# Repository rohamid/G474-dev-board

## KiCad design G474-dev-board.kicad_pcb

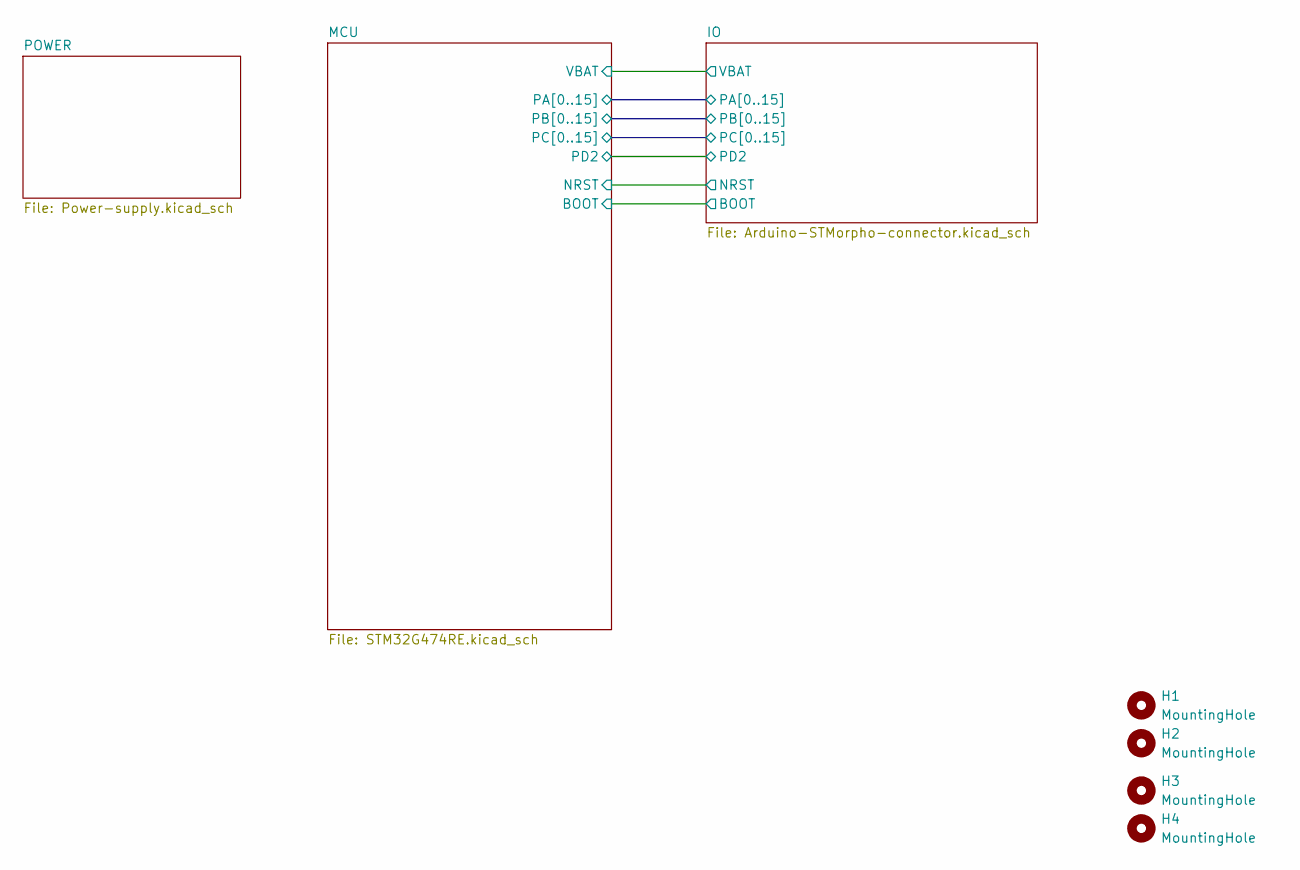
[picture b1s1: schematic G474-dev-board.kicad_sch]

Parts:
H1, H2, H3, H4: MountingHole; MountingHole_3.2mm_M3

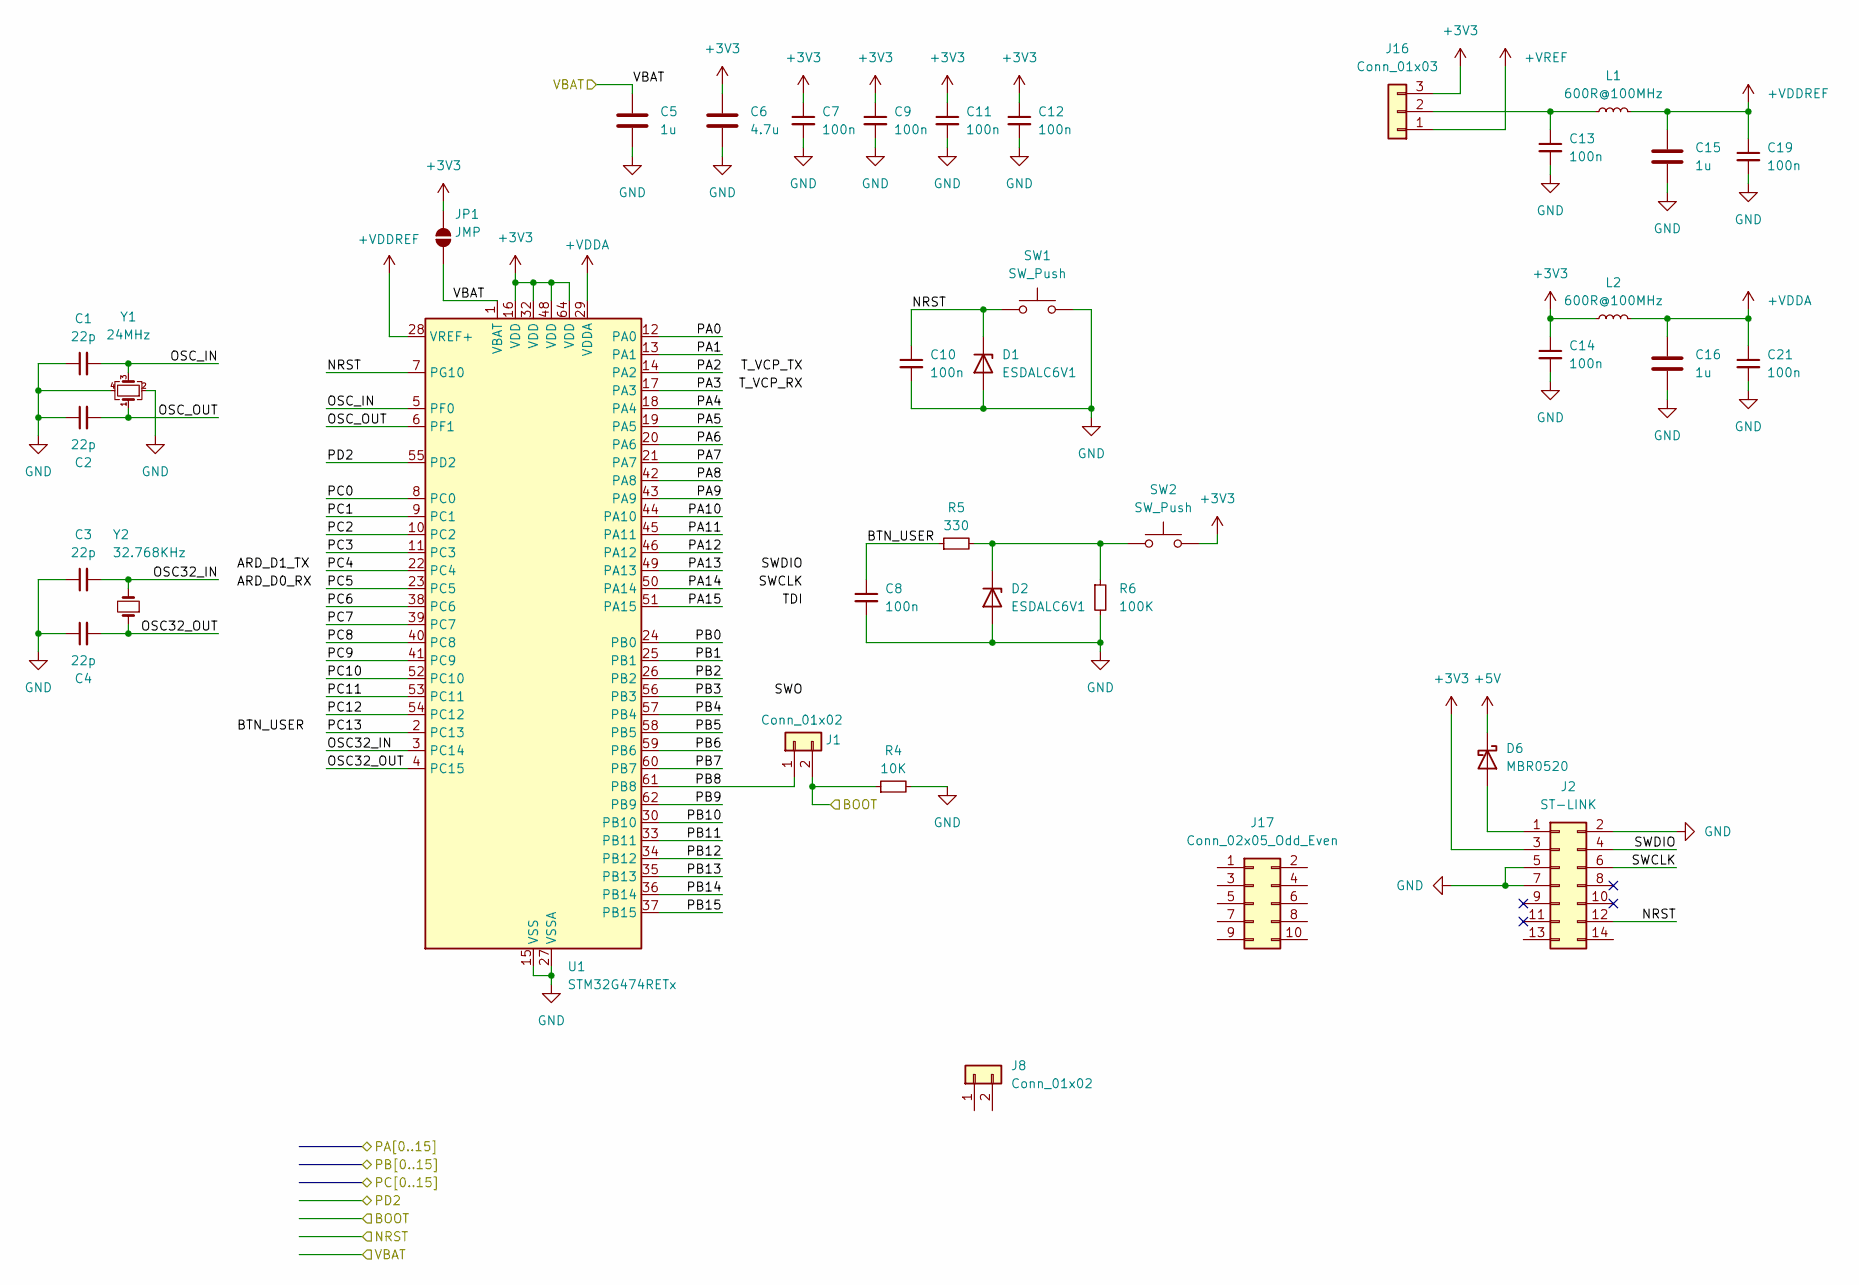
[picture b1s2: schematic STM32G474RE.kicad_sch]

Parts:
C1, C2, C3, C4: 22p; C_0603_1608Metric; JLCPCB Part # C1653
C5, C15, C16: 1u; C_0805_2012Metric; JLCPCB Part # C28323
C6: 4.7u; C_0805_2012Metric; JLCPCB Part # C1779
C7, C8, C9, C10, C11, C12, C13, C14, C19, C21: 100n; C_0603_1608Metric; JLCPCB Part # C14663
D1, D2: ESDALC6V1; D_SOD-123F; JLCPCB Part # C2990473
D6: MBR0520; D_SOD-123; JLCPCB Part # C64885
J1, J8: Conn_01x02; PinHeader_1x02_P2.54mm_Vertical
J2: ST-LINK; PinHeader_2x07_P1.27mm_Vertical_SMD
J16: Conn_01x03; PinHeader_1x03_P2.54mm_Vertical
J17: Conn_02x05_Odd_Even; IDC-Header_2x05_P2.54mm_Vertical
JP1: JMP; SolderJumper-2_P1.3mm_Open_RoundedPad1.0x1.5mm
L1, L2: 600R@100MHz; L_0805_2012Metric_Pad1.05x1.20mm_HandSolder; JLCPCB Part # C1017
R4: 10K; R_0603_1608Metric; JLCPCB Part # C25804
R5: 330; R_0603_1608Metric; JLCPCB Part # C23138
R6: 100K; R_0603_1608Metric; JLCPCB Part # C25803
SW1, SW2: SW_Push; SW_PUSH_6mm_H5mm
U1: STM32G474RETx; LQFP-64_10x10mm_P0.5mm; JLCPCB Part # C521608
Y1: 24MHz; Crystal_SMD_3225-4Pin_3.2x2.5mm; JLCPCB Part # C255917
Y2: 32.768KHz; Crystal_SMD_3215-2Pin_3.2x1.5mm; JLCPCB Part # C97606

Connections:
+3V3: C6.1, C7.1, C9.1, C11.1, C12.1, C14.1, J2.3, J16.3, JP1.2 (B), L2.1, SW2.2, U1.16 (VDD), U1.32 (VDD), U1.48 (VDD), U1.64 (VDD); also elsewhere on the board
+5V: D6.1 (K); also elsewhere on the board
+VDDA: C16.1, C21.1, L2.2, U1.29 (VDDA)
+VDDREF: C15.1, C19.1, L1.2, U1.28 (VREF+); also elsewhere on the board
+VREF: J16.1; also elsewhere on the board
/IO/BOOT: J1.2, R4.1; also elsewhere on the board
/IO/NRST: C10.1, D1.1 (K), J2.12, SW1.1, U1.7 (PG10); also elsewhere on the board
/IO/PA0: U1.12 (PA0); also elsewhere on the board
/IO/PA1: U1.13 (PA1); also elsewhere on the board
/IO/PA2: U1.14 (PA2)
/IO/PA3: U1.17 (PA3)
/IO/PA4: U1.18 (PA4); also elsewhere on the board
/IO/PA5: U1.19 (PA5); also elsewhere on the board
/IO/PA6: U1.20 (PA6); also elsewhere on the board
/IO/PA7: U1.21 (PA7); also elsewhere on the board
/IO/PA8: U1.42 (PA8); also elsewhere on the board
/IO/PA9: U1.43 (PA9); also elsewhere on the board
/IO/PA10: U1.44 (PA10); also elsewhere on the board
/IO/PA11: U1.45 (PA11); also elsewhere on the board
/IO/PA12: U1.46 (PA12); also elsewhere on the board
/IO/PA13: U1.49 (PA13); also elsewhere on the board
/IO/PA14: U1.50 (PA14); also elsewhere on the board
/IO/PA15: U1.51 (PA15); also elsewhere on the board
/IO/PB0: U1.24 (PB0); also elsewhere on the board
/IO/PB1: U1.25 (PB1); also elsewhere on the board
/IO/PB2: U1.26 (PB2); also elsewhere on the board
/IO/PB3: U1.56 (PB3); also elsewhere on the board
/IO/PB4: U1.57 (PB4); also elsewhere on the board
/IO/PB5: U1.58 (PB5); also elsewhere on the board
/IO/PB6: U1.59 (PB6); also elsewhere on the board
/IO/PB7: U1.60 (PB7); also elsewhere on the board
/IO/PB8: J1.1, U1.61 (PB8); also elsewhere on the board
/IO/PB9: U1.62 (PB9); also elsewhere on the board
/IO/PB10: U1.30 (PB10); also elsewhere on the board
/IO/PB11: U1.33 (PB11); also elsewhere on the board
/IO/PB12: U1.34 (PB12); also elsewhere on the board
/IO/PB13: U1.35 (PB13); also elsewhere on the board
/IO/PB14: U1.36 (PB14); also elsewhere on the board
/IO/PB15: U1.37 (PB15); also elsewhere on the board
/IO/PC0: U1.8 (PC0); also elsewhere on the board
/IO/PC1: U1.9 (PC1); also elsewhere on the board
/IO/PC2: U1.10 (PC2); also elsewhere on the board
/IO/PC3: U1.11 (PC3); also elsewhere on the board
/IO/PC4: U1.22 (PC4); also elsewhere on the board
/IO/PC5: U1.23 (PC5); also elsewhere on the board
/IO/PC6: U1.38 (PC6); also elsewhere on the board
/IO/PC7: U1.39 (PC7); also elsewhere on the board
/IO/PC8: U1.40 (PC8); also elsewhere on the board
/IO/PC9: U1.41 (PC9); also elsewhere on the board
/IO/PC10: U1.52 (PC10); also elsewhere on the board
/IO/PC11: U1.53 (PC11); also elsewhere on the board
/IO/PC12: U1.54 (PC12); also elsewhere on the board
/IO/PC13: U1.2 (PC13); also elsewhere on the board
/IO/PD2: U1.55 (PD2); also elsewhere on the board
/MCU/BTN_USER: C8.1, R5.1
/MCU/OSC32_IN: C3.2, U1.3 (PC14), Y2.2
/MCU/OSC32_OUT: C4.2, U1.4 (PC15), Y2.1
/MCU/OSC_IN: C1.2, U1.5 (PF0), Y1.3
/MCU/OSC_OUT: C2.2, U1.6 (PF1), Y1.1
/MCU/SWCLK: J2.6
/MCU/SWDIO: J2.4
/MCU/VBAT: C5.1, JP1.1 (A), U1.1 (VBAT); also elsewhere on the board
GND: C1.1, C2.1, C3.1, C4.1, C5.2, C6.2, C7.2, C8.2, C9.2, C10.2, C11.2, C12.2, C13.2, C14.2, C15.2, C16.2, C19.2, C21.2, D1.2 (A), D2.2 (A), J2.2, J2.5, J2.7, R4.2, R6.2, SW1.2, U1.15 (VSS), U1.27 (VSSA), U1.31 (VSS), U1.47 (VSS), U1.63 (VSS), Y1.2, Y1.4; also elsewhere on the board
unnamed: D2.1 (K), R5.2, R6.1, SW2.1
unnamed: D6.2 (A), J2.1
unnamed: C13.1, J16.2, L1.1

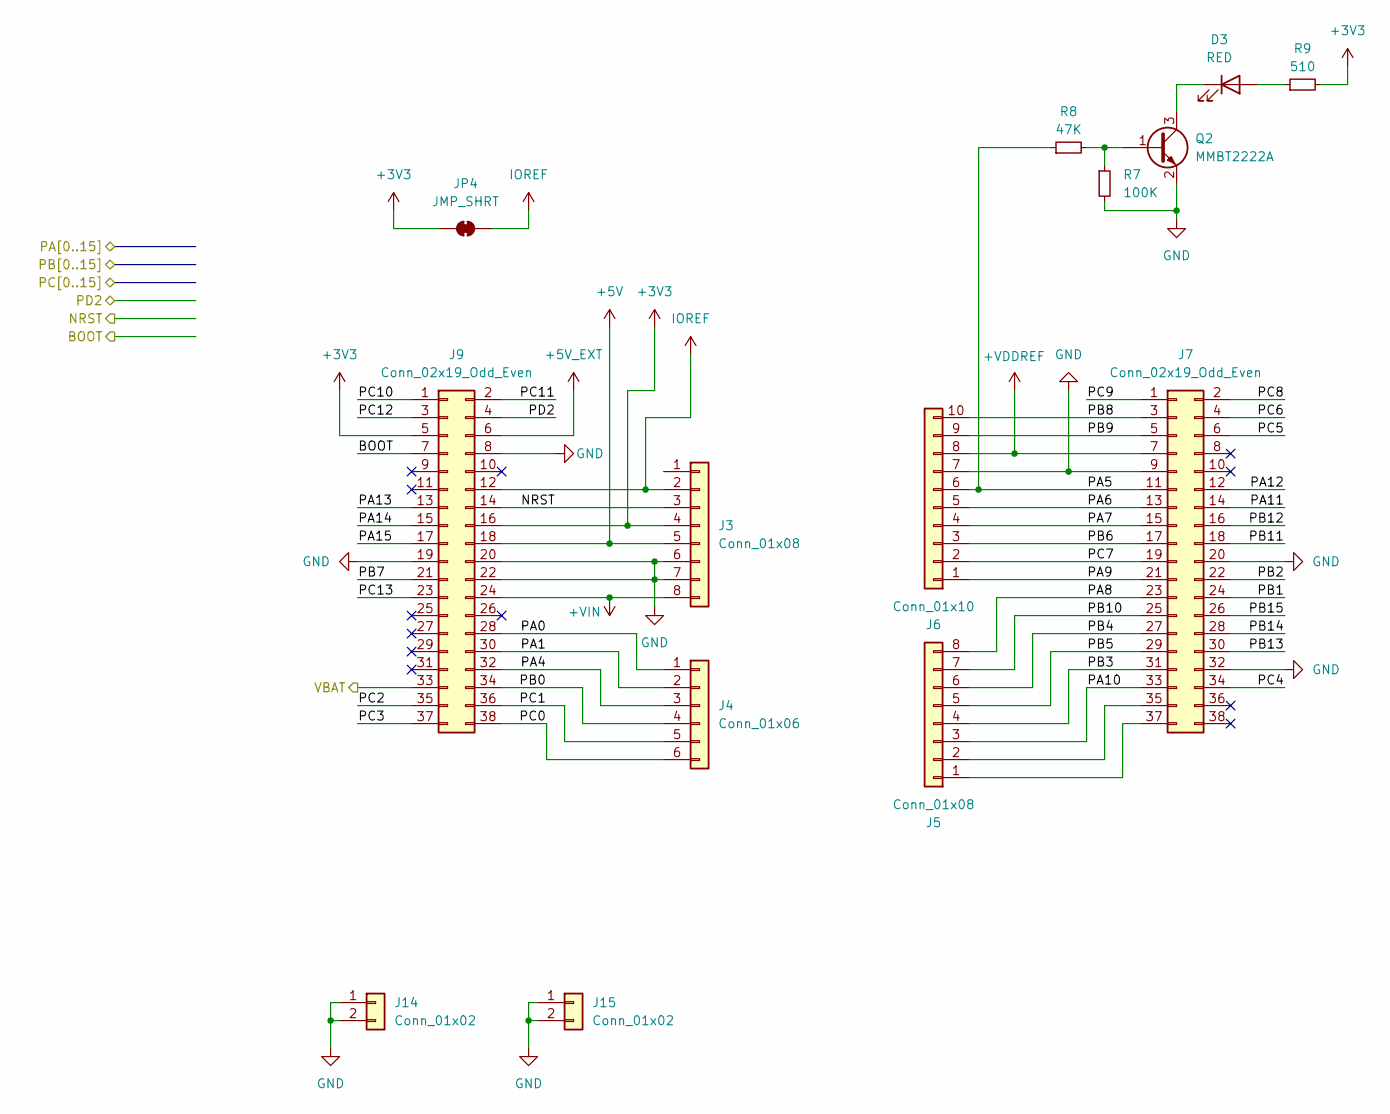
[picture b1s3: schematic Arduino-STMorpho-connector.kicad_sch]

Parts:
D3: RED; LED_0805_2012Metric; JLCPCB Part # C84256
J3, J5: Conn_01x08; PinSocket_1x08_P2.54mm_Vertical
J4: Conn_01x06; PinSocket_1x06_P2.54mm_Vertical
J6: Conn_01x10; PinSocket_1x10_P2.54mm_Vertical
J7, J9: Conn_02x19_Odd_Even; PinHeader_2x19_P2.54mm_Vertical
J14, J15: Conn_01x02; PinHeader_1x02_P2.54mm_Vertical
JP4: JMP_SHRT; SolderJumper-2_P1.3mm_Bridged_RoundedPad1.0x1.5mm
Q2: MMBT2222A; SOT-23; JLCPCB Part # C82460
R7: 100K; R_0603_1608Metric; JLCPCB Part # C25803
R8: 47K; R_0603_1608Metric; JLCPCB Part # C25819
R9: 510; R_0603_1608Metric; JLCPCB Part # C23193

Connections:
+3V3: J3.4, J9.5, J9.16, JP4.2 (B), R9.2; also elsewhere on the board
+5V: J3.5, J9.18; also elsewhere on the board
+5V_EXT: J9.6; also elsewhere on the board
+VDDREF: J6.8, J7.7; also elsewhere on the board
+VIN: J3.8, J9.24; also elsewhere on the board
/IO/BOOT: J9.7; also elsewhere on the board
/IO/NRST: J3.3, J9.14; also elsewhere on the board
/IO/PA0: J4.1, J9.28; also elsewhere on the board
/IO/PA1: J4.2, J9.30; also elsewhere on the board
/IO/PA4: J4.3, J9.32; also elsewhere on the board
/IO/PA5: J6.6, J7.11, R8.1; also elsewhere on the board
/IO/PA6: J6.5, J7.13; also elsewhere on the board
/IO/PA7: J6.4, J7.15; also elsewhere on the board
/IO/PA8: J5.8, J7.23; also elsewhere on the board
/IO/PA9: J6.1, J7.21; also elsewhere on the board
/IO/PA10: J5.3, J7.33; also elsewhere on the board
/IO/PA11: J7.14; also elsewhere on the board
/IO/PA12: J7.12; also elsewhere on the board
/IO/PA13: J9.13; also elsewhere on the board
/IO/PA14: J9.15; also elsewhere on the board
/IO/PA15: J9.17; also elsewhere on the board
/IO/PB0: J4.4, J9.34; also elsewhere on the board
/IO/PB1: J7.24; also elsewhere on the board
/IO/PB2: J7.22; also elsewhere on the board
/IO/PB3: J5.4, J7.31; also elsewhere on the board
/IO/PB4: J5.6, J7.27; also elsewhere on the board
/IO/PB5: J5.5, J7.29; also elsewhere on the board
/IO/PB6: J6.3, J7.17; also elsewhere on the board
/IO/PB7: J9.21; also elsewhere on the board
/IO/PB8: J6.10, J7.3; also elsewhere on the board
/IO/PB9: J6.9, J7.5; also elsewhere on the board
/IO/PB10: J5.7, J7.25; also elsewhere on the board
/IO/PB11: J7.18; also elsewhere on the board
/IO/PB12: J7.16; also elsewhere on the board
/IO/PB13: J7.30; also elsewhere on the board
/IO/PB14: J7.28; also elsewhere on the board
/IO/PB15: J7.26; also elsewhere on the board
/IO/PC0: J4.6, J9.38; also elsewhere on the board
/IO/PC1: J4.5, J9.36; also elsewhere on the board
/IO/PC2: J9.35; also elsewhere on the board
/IO/PC3: J9.37; also elsewhere on the board
/IO/PC4: J7.34; also elsewhere on the board
/IO/PC5: J7.6; also elsewhere on the board
/IO/PC6: J7.4; also elsewhere on the board
/IO/PC7: J6.2, J7.19; also elsewhere on the board
/IO/PC8: J7.2; also elsewhere on the board
/IO/PC9: J7.1; also elsewhere on the board
/IO/PC10: J9.1; also elsewhere on the board
/IO/PC11: J9.2; also elsewhere on the board
/IO/PC12: J9.3; also elsewhere on the board
/IO/PC13: J9.23; also elsewhere on the board
/IO/PD2: J9.4; also elsewhere on the board
/MCU/VBAT: J9.33; also elsewhere on the board
GND: J3.6, J3.7, J6.7, J7.9, J7.20, J7.32, J9.8, J9.19, J9.20, J9.22, J14.1, J14.2, J15.1, J15.2, Q2.2 (E), R7.2; also elsewhere on the board
IOREF: J3.2, J9.12, JP4.1 (A)
unnamed: D3.2 (A), R9.1
unnamed: D3.1 (K), Q2.3 (C)
unnamed: J5.1, J7.37
unnamed: J5.2, J7.35
unnamed: Q2.1 (B), R7.1, R8.2

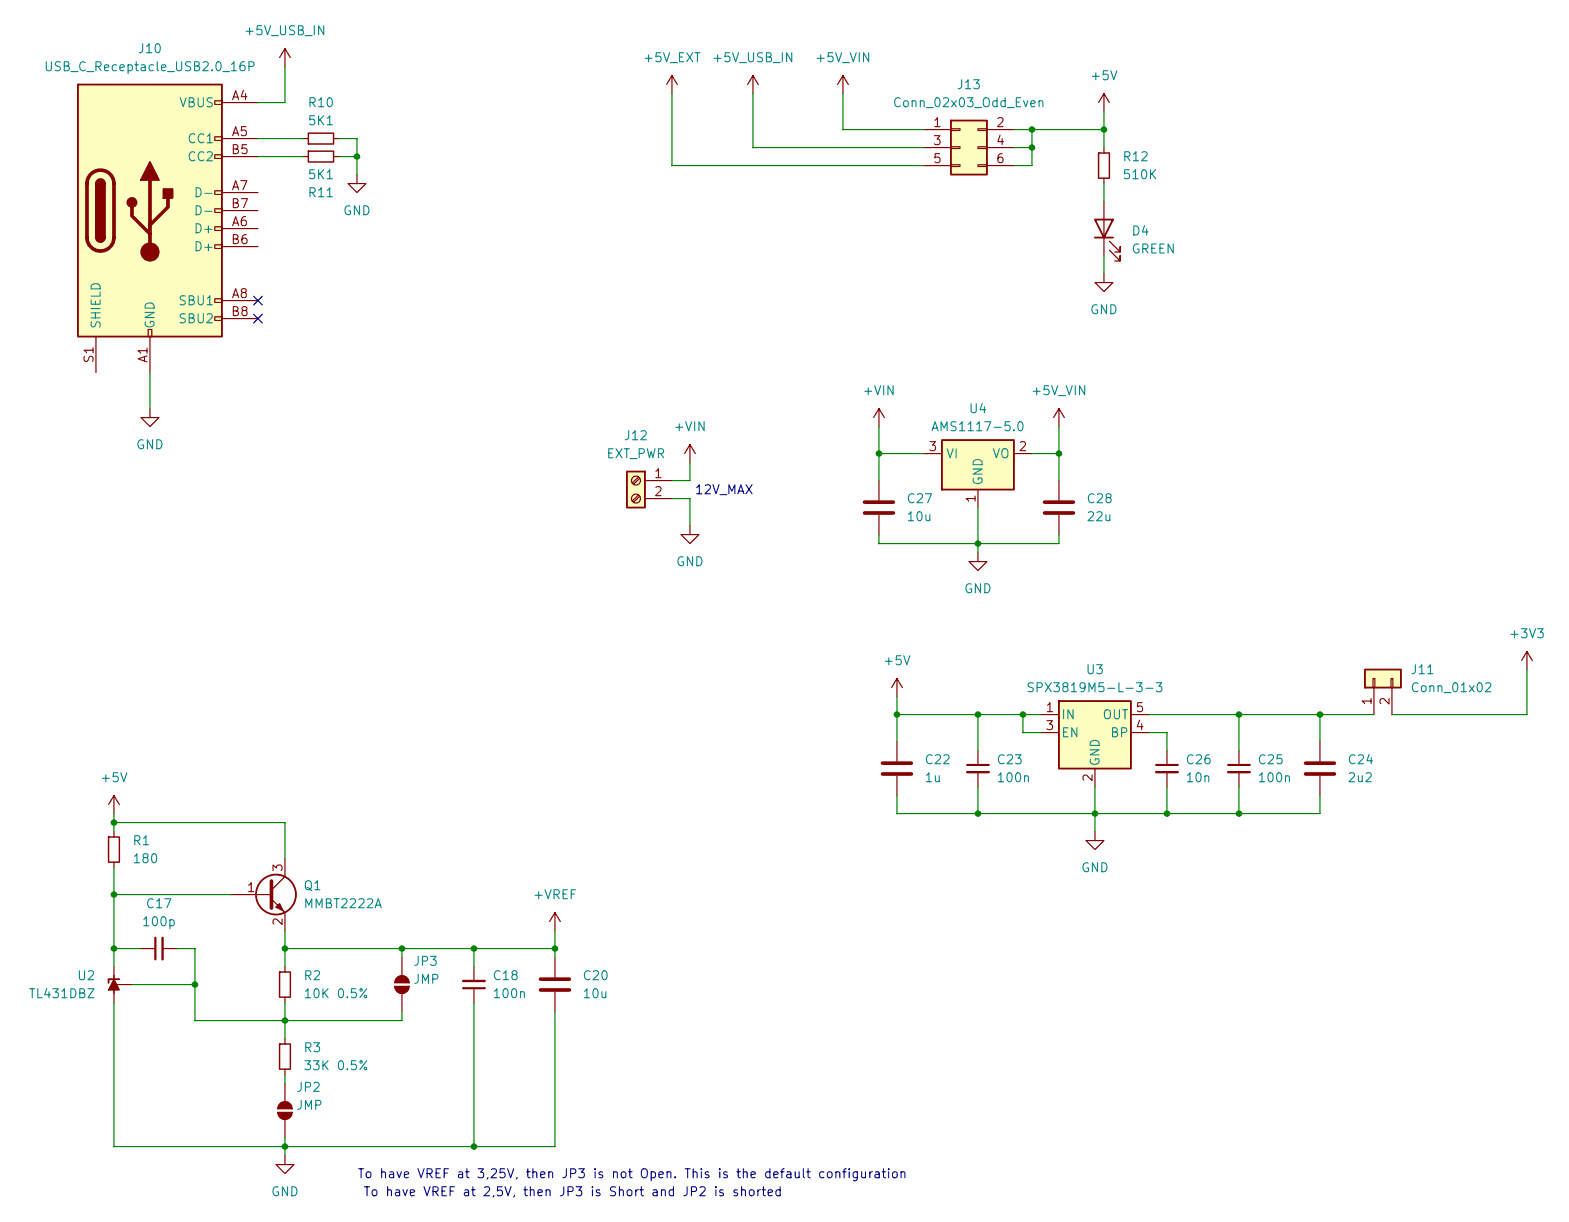
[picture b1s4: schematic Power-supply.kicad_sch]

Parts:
C17: 100p; C_0603_1608Metric; JLCPCB Part # C14858
C18, C23, C25: 100n; C_0603_1608Metric; JLCPCB Part # C14663
C20, C27: 10u; C_0805_2012Metric; JLCPCB Part # C440198
C22: 1u; C_0805_2012Metric; JLCPCB Part # C28323
C24: 2u2; C_0805_2012Metric; JLCPCB Part # C377773
C26: 10n; C_0603_1608Metric; JLCPCB Part # C57112
C28: 22u; C_0805_2012Metric; JLCPCB Part # C45783
D4: GREEN; LED_0805_2012Metric; JLCPCB Part # C2297
J10: USB_C_Receptacle_USB2.0_16P; USB_C_Receptacle_G-Switch_GT-USB-7010ASV; JLCPCB Part # C2988369
J11: Conn_01x02; PinHeader_1x02_P2.54mm_Vertical
J12: EXT_PWR; TerminalBlock_bornier-2_P5.08mm
J13: Conn_02x03_Odd_Even; PinHeader_2x03_P2.54mm_Vertical
JP2, JP3: JMP; SolderJumper-2_P1.3mm_Open_RoundedPad1.0x1.5mm
Q1: MMBT2222A; SOT-23; JLCPCB Part # C82460
R1: 180; R_0603_1608Metric; JLCPCB Part # C22828
R2: 10K 0.5%; R_0603_1608Metric; JLCPCB Part # C227439
R3: 33K 0.5%; R_0603_1608Metric; JLCPCB Part # C227486
R10, R11: 5K1; R_0603_1608Metric; JLCPCB Part # C23186
R12: 510K; R_0603_1608Metric; JLCPCB Part # C23192
U2: TL431DBZ; SOT-23; JLCPCB Part # C23892
U3: SPX3819M5-L-3-3; SOT-23-5; JLCPCB Part # C5370980
U4: AMS1117-5.0; SOT-223-3_TabPin2; JLCPCB Part # C6187

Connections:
+3V3: J11.2; also elsewhere on the board
+5V: C22.1, C23.1, J13.2, J13.4, J13.6, Q1.3 (C), R1.1, R12.1, U3.1 (IN), U3.3 (EN); also elsewhere on the board
+5V_EXT: J13.5; also elsewhere on the board
+5V_USB_IN: J10.A4 (VBUS), J10.A9 (VBUS), J10.B4 (VBUS), J10.B9 (VBUS), J13.3
+5V_VIN: C28.1, J13.1, U4.2 (VO)
+VIN: C27.1, J12.1, U4.3 (VI); also elsewhere on the board
+VREF: C18.2, C20.1, JP3.2 (B), Q1.2 (E), R2.1; also elsewhere on the board
GND: C18.1, C20.2, C22.2, C23.2, C24.2, C25.2, C26.2, C27.2, C28.2, D4.1 (K), J10.A1 (GND), J10.A12 (GND), J10.B1 (GND), J10.B12 (GND), J12.2, JP2.1 (A), R10.2, R11.2, U2.3 (A), U3.2 (GND), U4.1 (GND); also elsewhere on the board
unnamed: D4.2 (A), R12.2
unnamed: J10.A5 (CC1), R10.1
unnamed: J10.B5 (CC2), R11.1
unnamed: C24.1, C25.1, J11.1, U3.5 (OUT)
unnamed: JP2.2 (B), R3.2
unnamed: C17.2, JP3.1 (A), R2.2, R3.1, U2.2 (REF)
unnamed: C17.1, Q1.1 (B), R1.2, U2.1 (K)
unnamed: C26.1, U3.4 (BP)

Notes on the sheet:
To have VREF at 2,5V, then JP3 is Short and JP2 is shorted
To have VREF at 3,25V, then JP3 is not Open. This is the default configuration
12V_MAX

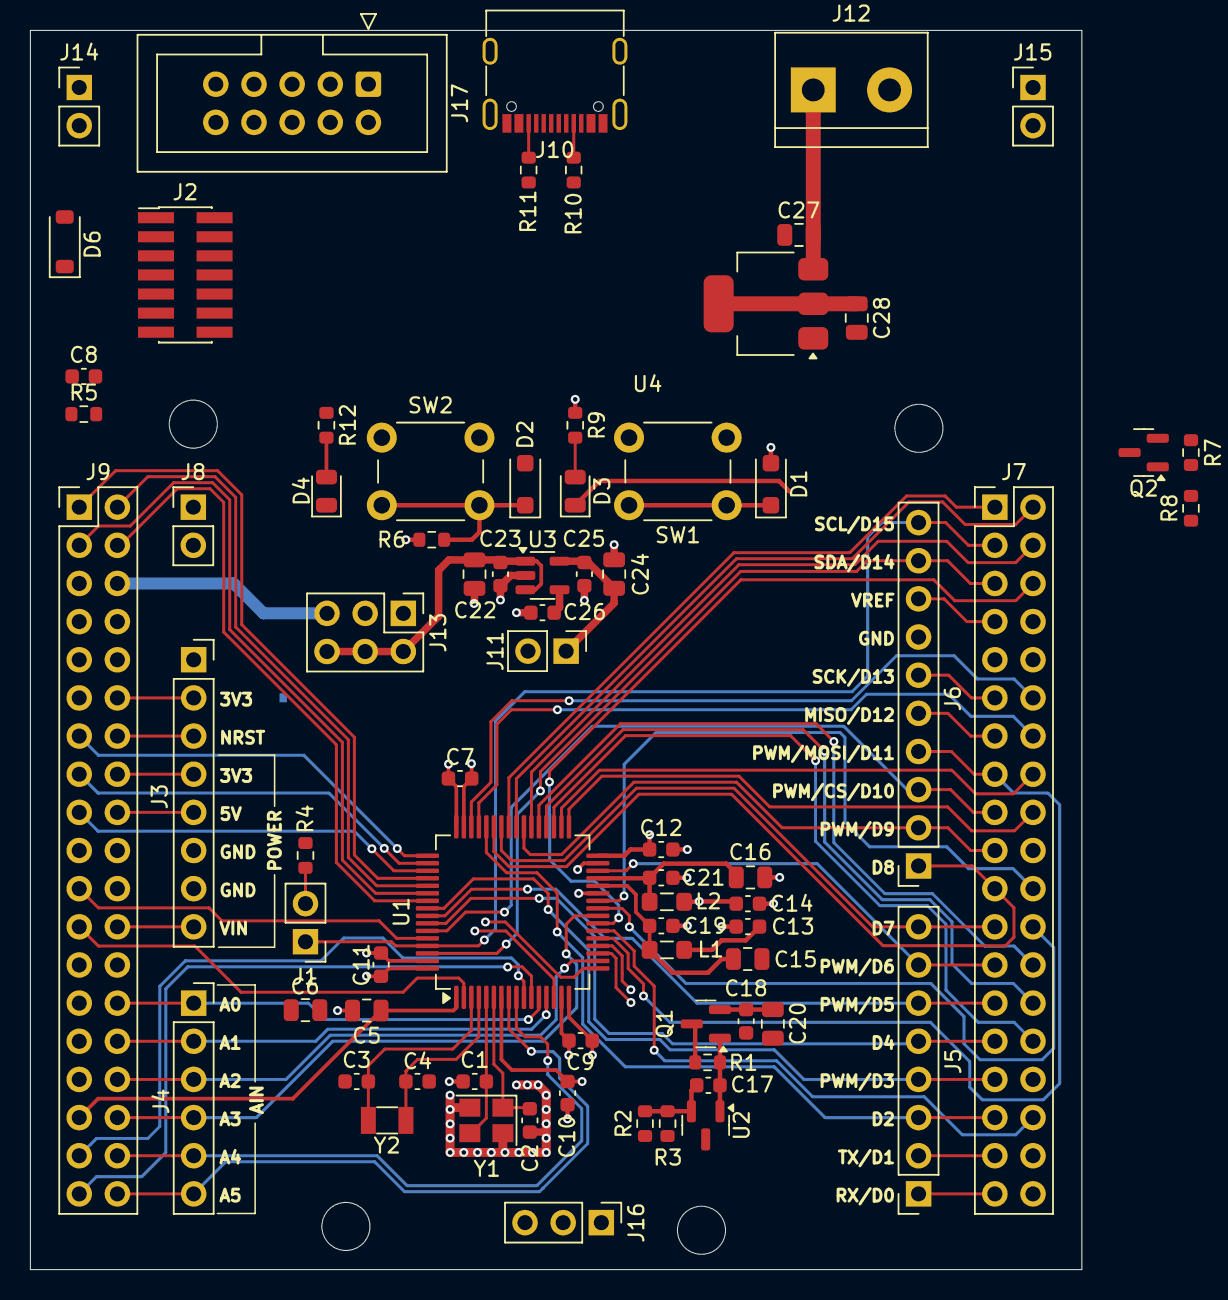
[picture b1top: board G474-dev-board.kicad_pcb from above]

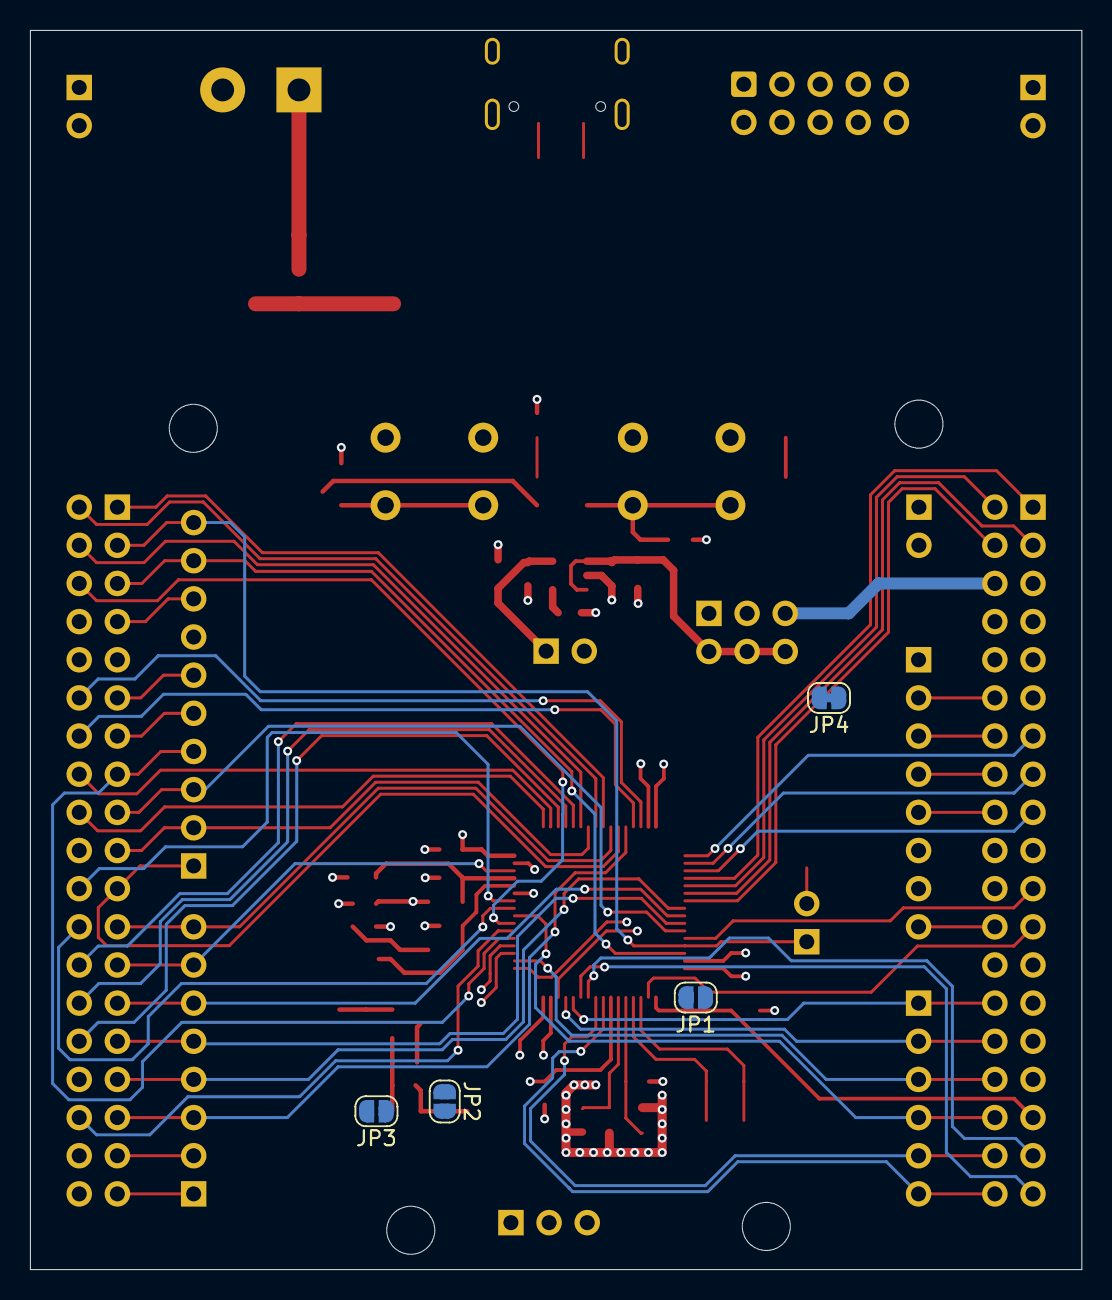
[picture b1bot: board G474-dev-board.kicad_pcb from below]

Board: 4 copper layers, 70.0 x 82.5 mm, 82 parts (4 on the bottom side), 80 nets.

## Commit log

2024-12-11 SMD part number assigned, relocate MCU sch to hierarcical sheet
2024-12-12 no changes
2024-12-15 IO tracks routed, 2 pin left
